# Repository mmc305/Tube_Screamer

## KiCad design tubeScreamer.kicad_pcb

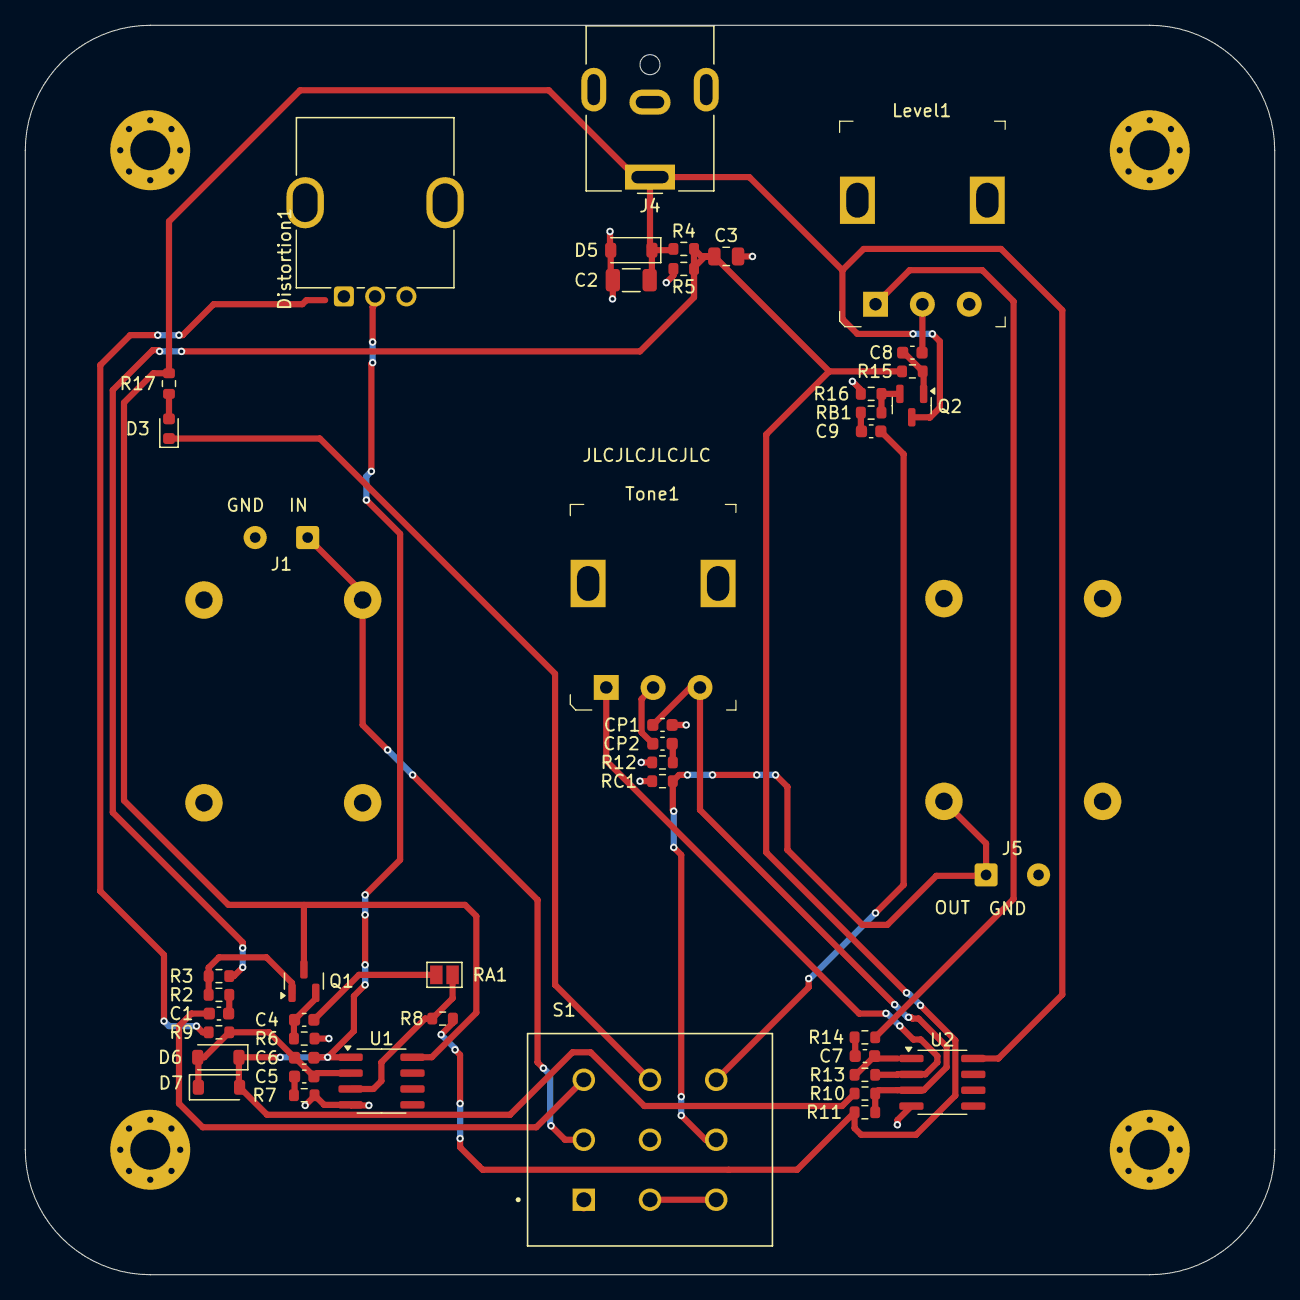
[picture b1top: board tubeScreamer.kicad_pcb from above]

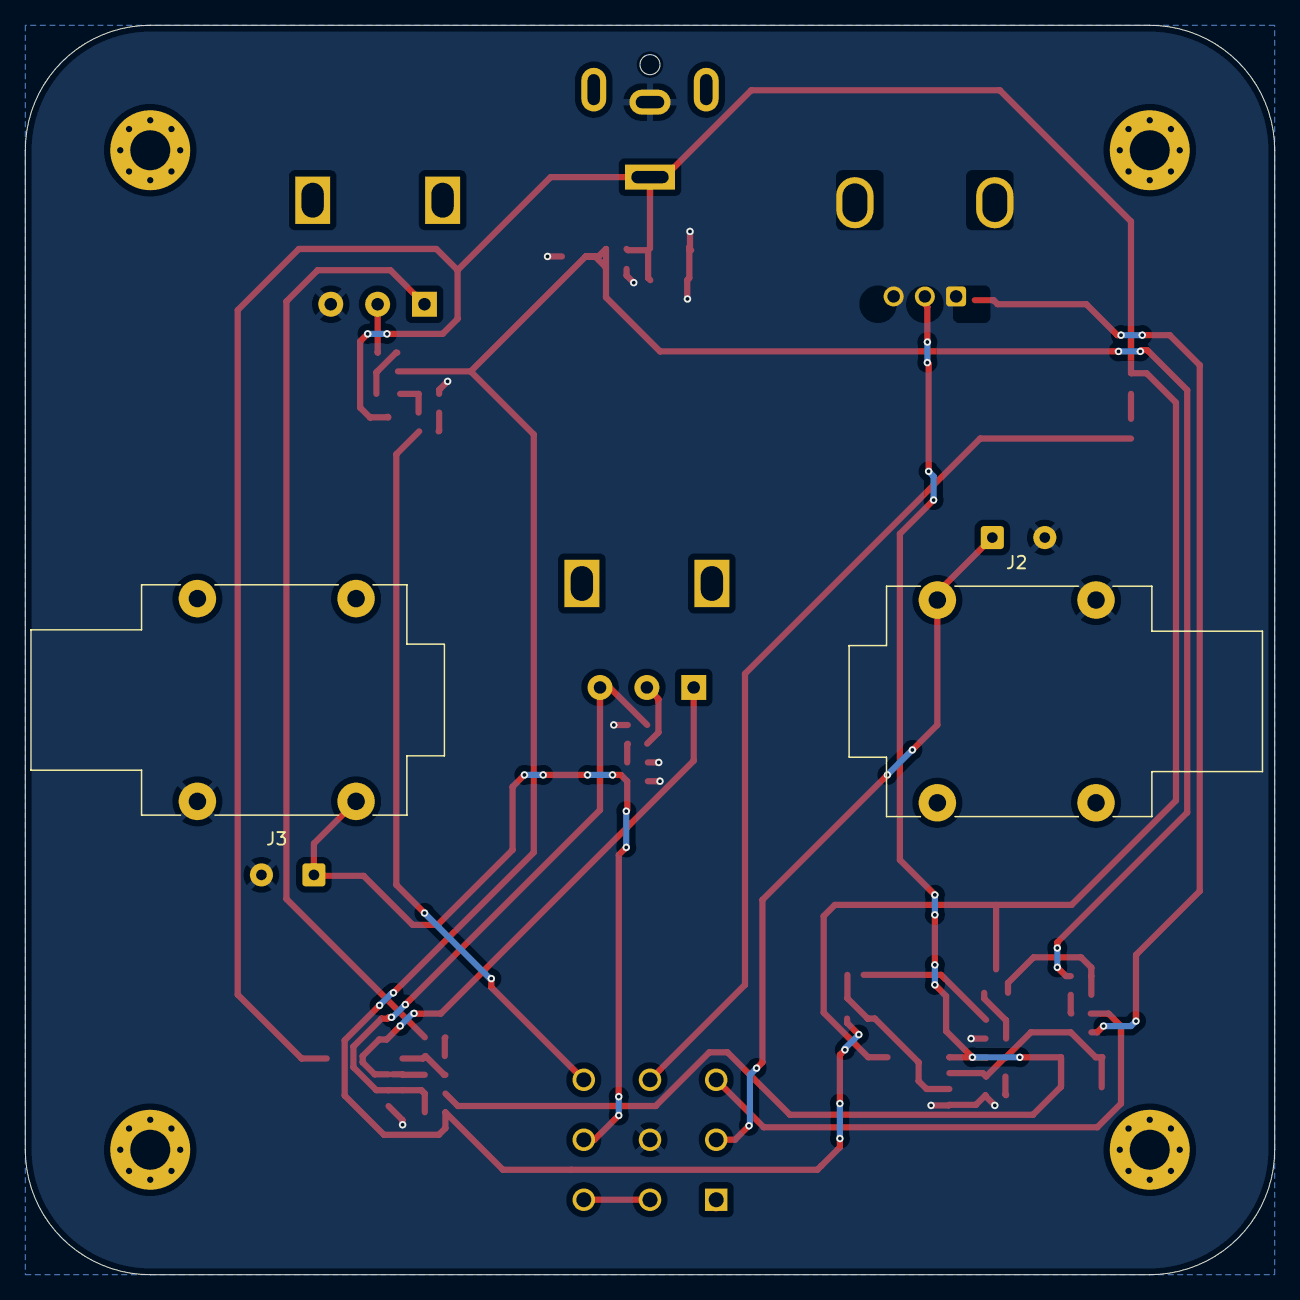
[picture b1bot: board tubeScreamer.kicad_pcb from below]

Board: 2 copper layers, 100.0 x 100.0 mm, 51 parts (2 on the bottom side), 29 nets.

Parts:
C1: 20nF; C_0603_1608Metric
C2: 100uF; C_1206_3216Metric
C3: 47uF; C_0805_2012Metric
C4, C7: 1uF; C_0603_1608Metric
C5: 47nF; C_0603_1608Metric
C6: 51pF; C_0603_1608Metric
C8: 100nF; C_0603_1608Metric
C9: 10uF; C_0603_1608Metric
CP1, CP2: 220nF; C_0603_1608Metric
D3: LED; LED_0603_1608Metric
D5, D6, D7: 1N4148W; D_SOD-123
Distortion1: 500k Log; RotaryEncoder_Bourns_Vertical_PEC12R-3x17F-Nxxxx
H1, H2, H3, H4: MountingHole; MountingHole_3.2mm_M3_Pad_Via
J1: IN; SolderWire-0.25sqmm_1x02_P4.2mm_D0.65mm_OD1.7mm
J2: IN; Jack_6.35mm_Neutrik_NMJ4HFD2_Horizontal
J3: OUT; Jack_6.35mm_Neutrik_NMJ4HFD2_Horizontal
J4: 9V IN; BarrelJack_CUI_PJ-063AH_Horizontal
J5: OUT; SolderWire-0.25sqmm_1x02_P4.2mm_D0.65mm_OD1.7mm
Level1: 100k; Potentiometer_P120PK-Y25BR10K
Q1, Q2: MMBT2222A; SOT-23
R2, R10, R13, R14, R17: 1k; R_0603_1608Metric
R3, R15: 510k; R_0603_1608Metric
R4, R5: 10K; R_0603_1608Metric
R6, R8, R11, R16: 10k; R_0603_1608Metric
R7: 4.7k; R_0603_1608Metric
R9: 51k; R_0603_1608Metric
R12: 220; R_0603_1608Metric
RA1: 0; SolderJumper-2_P1.3mm_Open_Pad1.0x1.5mm
RB1: 10k; R_0603_1608Metric
RC1: 10k; R_0603_1608Metric
S1: Foot Switch; SW_FS57003PLT2B2M2QE
Tone1: 20k; Potentiometer_P120PK-Y25BR10K
U1, U2: TL072; SOIC-8_3.9x4.9mm_P1.27mm

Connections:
4.5V: C3.1, R3.2, R4.2, R5.1, R8.1, R11.2, R15.1
9V: C2.1, D5.1 (K), J4.1, Q1.3 (C), Q2.3 (C), R4.1, R17.2, U1.8 (VCC+), U2.8 (VCC+)
GND: C2.2, C3.2, CP1.2, D5.2 (A), J1.2, J2.S, J3.S, J4.2, J5.2, Level1.3, R5.2, R6.1, R7.1, R12.1, R16.2, RC1.2, S1.5, U1.4 (VCC-), U2.4 (VCC-)
IN: J1.1, J2.T, S1.2
unnamed: C1.1, S1.3
unnamed: C1.2, R2.1
unnamed: C4.2, RA1.1
unnamed: C5.1, R7.2
unnamed: C7.1, R13.2, U2.1
unnamed: C7.2, R14.1
unnamed: C8.1, Level1.2
unnamed: C9.1, RB1.1
unnamed: C9.2, S1.9
unnamed: CP1.1, R10.2, R11.1, Tone1.3, U2.3
unnamed: CP2.1, Tone1.2
unnamed: CP2.2, R12.2
unnamed: D3.2 (A), R17.1
unnamed: D3.1 (K), S1.6
unnamed: C5.2, C6.1, D6.2 (A), D7.1 (K), R9.1, U1.2
unnamed: C6.2, D6.1 (K), D7.2 (A), R10.1, U1.1
unnamed: Level1.1, R14.2
unnamed: Q1.1 (B), R2.2, R3.1
unnamed: C4.1, Q1.2 (E), R6.2
unnamed: C8.2, Q2.1 (B), R15.2
unnamed: Q2.2 (E), R16.1, RB1.2
unnamed: R8.2, RA1.2, U1.3
unnamed: R13.1, Tone1.1, U2.2
unnamed: S1.4, S1.7
OUT: J3.T, J5.1, RC1.1, S1.8

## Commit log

2025-06-12 init
2025-06-12 test commit
